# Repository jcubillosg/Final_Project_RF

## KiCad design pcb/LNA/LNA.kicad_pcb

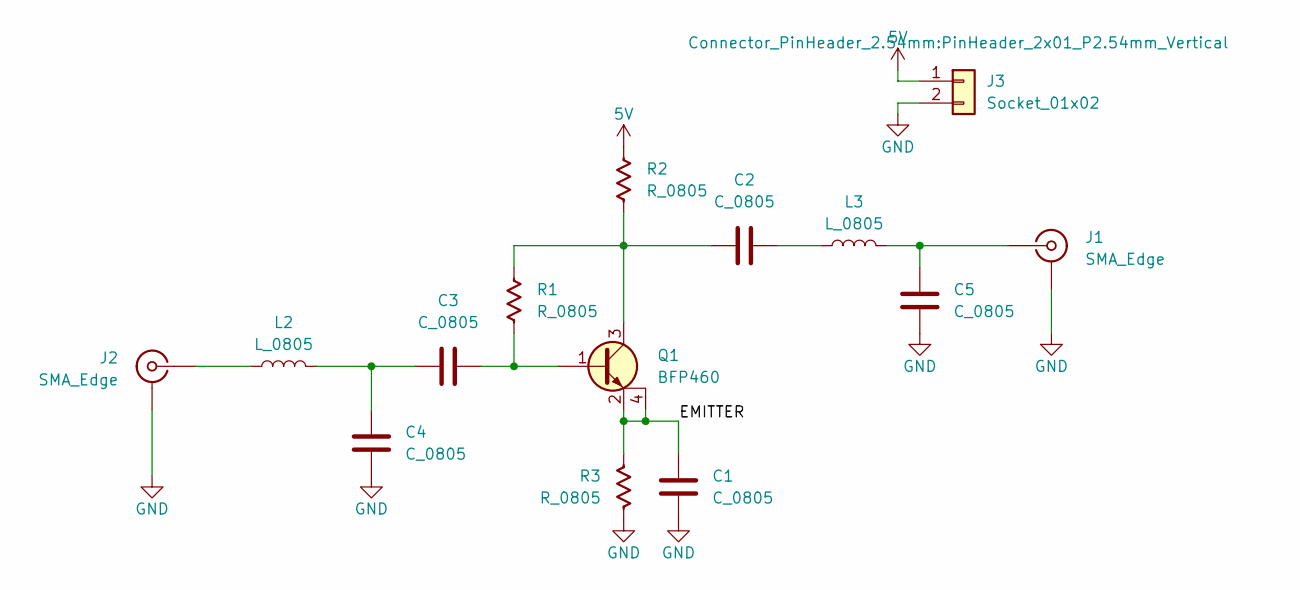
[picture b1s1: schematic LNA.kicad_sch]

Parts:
C1, C2, C3, C4, C5: C_0805; C_0805_2012Metric
J1, J2: SMA_Edge; SMA_Edge_8mm
J3: Socket_01x02; PinHeader_2x01_P2.54mm_Vertical; Part Number ?
L2, L3: L_0805; 0805
Q1: BFP460; SOT-343_SC-70-4
R1, R2, R3: R_0805; R_0805_2012Metric

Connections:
5V: J3.1, R2.1
/EMITTER: C1.1, Q1.2 (E), Q1.4 (E), R3.1
GND: C1.2, C4.2, C5.1, J1.2 (Ext), J2.2 (Ext), J3.2, R3.2
unnamed: C2.2, L3.1
unnamed: C3.1, C4.1, L2.2
unnamed: C5.2, J1.1 (In), L3.2
unnamed: J2.1 (In), L2.1
unnamed: C3.2, Q1.1 (B), R1.2
unnamed: C2.1, Q1.3 (C), R1.1, R2.2

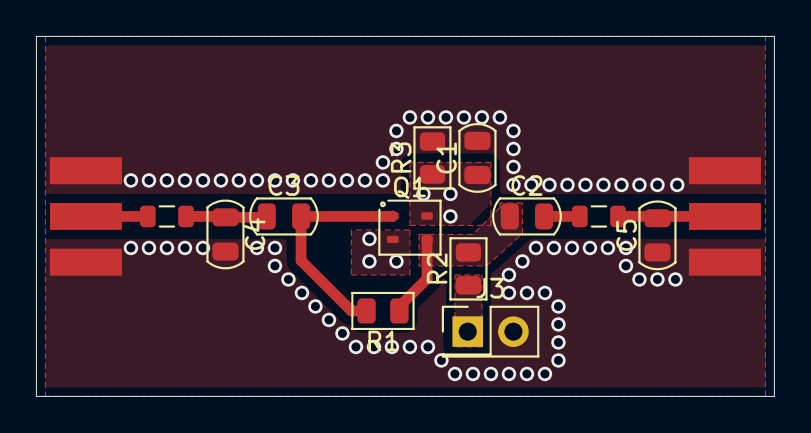
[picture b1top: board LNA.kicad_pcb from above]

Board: 2 copper layers, 41.0 x 20.0 mm, 14 parts (0 on the bottom side), 9 nets.

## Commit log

2025-10-31 First presentation
2025-11-09 Modified LNA schematics, added better comparison between s2p and SPICE models
2025-11-11 Added parameter circles, improved simulations
2025-11-21 Finished routing with 0805 components
